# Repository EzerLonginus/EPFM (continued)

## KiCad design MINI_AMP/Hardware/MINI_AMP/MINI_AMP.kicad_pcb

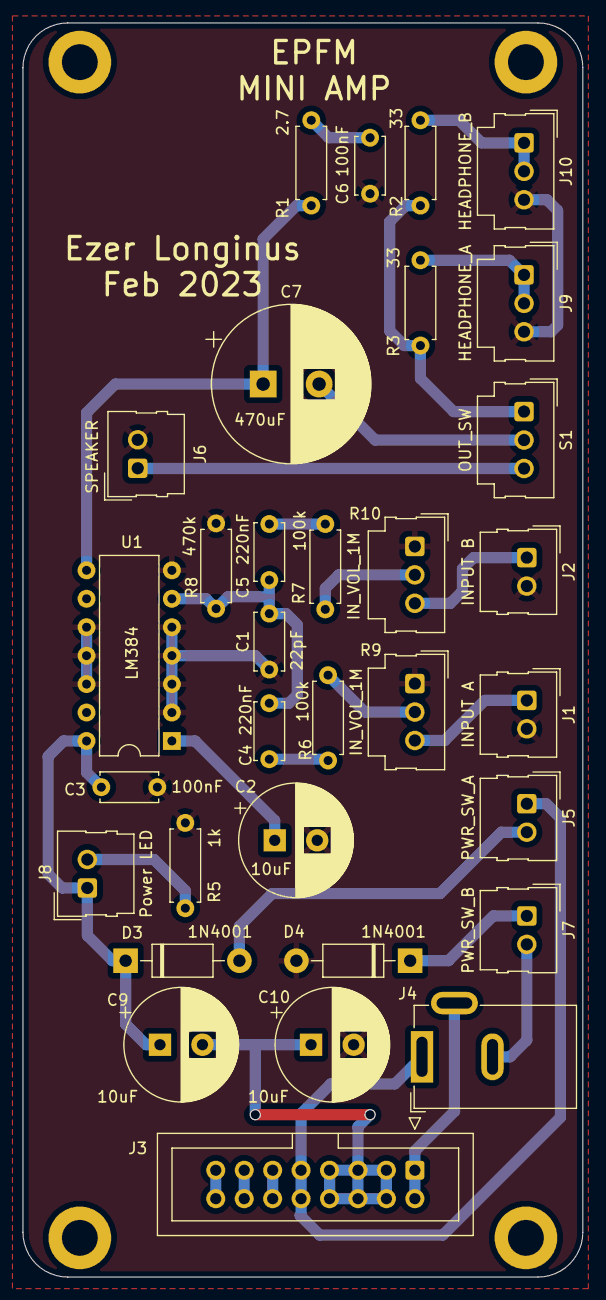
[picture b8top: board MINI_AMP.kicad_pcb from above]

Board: 2 copper layers, 50.0 x 112.0 mm, 36 parts (0 on the bottom side), 27 nets.

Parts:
C1: 22pF; C_Disc_D5.0mm_W2.5mm_P5.00mm
C2, C9, C10: 10uF; CP_Radial_D10.0mm_P3.80mm
C3, C6: 100nF; C_Disc_D5.0mm_W2.5mm_P5.00mm
C4, C5: 220nF; C_Disc_D5.0mm_W2.5mm_P5.00mm
C7: 470uF; CP_Radial_D14.0mm_P5.00mm
D3, D4: 1N4001; D_DO-41_SOD81_P10.16mm_Horizontal
H1, H2, H3, H4: MountingHole; MountingHole_3.2mm_M3_DIN965_Pad
J1: INPUT A; Molex_SL_171971-0002_1x02_P2.54mm_Vertical
J2: INPUT B; Molex_SL_171971-0002_1x02_P2.54mm_Vertical
J3: Conn_02x08_Odd_Even; IDC-Header_2x08_P2.54mm_Vertical
J4: Barrel_Jack_Switch; BarrelJack_GCT_DCJ200-10-A_Horizontal
J5: PWR_SW_A; Molex_SL_171971-0002_1x02_P2.54mm_Vertical
J6: SPEAKER; Molex_SL_171971-0002_1x02_P2.54mm_Vertical
J7: PWR_SW_B; Molex_SL_171971-0002_1x02_P2.54mm_Vertical
J8: Power LED; Molex_SL_171971-0002_1x02_P2.54mm_Vertical
J9: HEADPHONE_A; Molex_SL_171971-0003_1x03_P2.54mm_Vertical
J10: HEADPHONE_B; Molex_SL_171971-0003_1x03_P2.54mm_Vertical
R1: 2.7; R_Axial_DIN0207_L6.3mm_D2.5mm_P7.62mm_Horizontal
R2, R3: 33; R_Axial_DIN0207_L6.3mm_D2.5mm_P7.62mm_Horizontal
R5: 1k; R_Axial_DIN0207_L6.3mm_D2.5mm_P7.62mm_Horizontal
R6, R7: 100k; R_Axial_DIN0207_L6.3mm_D2.5mm_P7.62mm_Horizontal
R8: 470k; R_Axial_DIN0207_L6.3mm_D2.5mm_P7.62mm_Horizontal
R9, R10: IN_VOL_1M; Molex_SL_171971-0003_1x03_P2.54mm_Vertical
S1: OUT_SW; Molex_SL_171971-0003_1x03_P2.54mm_Vertical
U1: LM384; DIP-14_W7.62mm

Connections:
+5V: J3.11, J3.12
+12V: J3.9, J3.10, J4.1, J5.1
+24V: C3.2, C9.1, D3.1 (K), J8.1, U1.14 (VS)
-12V: J4.2, J7.2
CV: J3.13, J3.14
Earth: C1.1, C2.2, C3.1, C6.1, C10.2, D4.2 (A), J1.2, J2.2, J6.2, J9.3, J10.3, R5.1, R8.1, R9.1, R10.1, U1.2 (+), U1.3 (GND), U1.4 (GND), U1.5 (GND), U1.7 (GND), U1.10 (GND), U1.11 (GND), U1.12 (GND)
GATE: J3.15, J3.16
unnamed: C2.1, U1.1 (BYPASS)
unnamed: C1.2, C4.1, C5.1, R8.2, U1.6 (-)
unnamed: C6.2, R1.1
unnamed: C7.1, R1.2, U1.8
unnamed: C7.2, S1.2
unnamed: C9.2, C10.1, J3.3, J3.4, J3.5, J3.6, J3.7, J3.8
unnamed: D3.2 (A), J5.2
unnamed: D4.1 (K), J7.1
unnamed: J2.1, R10.3
unnamed: J3.1, J3.2, J4.3
unnamed: J6.1, S1.3
unnamed: J8.2, R5.2
unnamed: J9.1, J9.2, R3.1
unnamed: J10.1, J10.2, R2.1
unnamed: R2.2, R3.2, S1.1
unnamed: C4.2, R6.2
unnamed: C5.2, R7.2
unnamed: R6.1, R9.2
unnamed: J1.1, R9.3
unnamed: R7.1, R10.2

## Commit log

2023-01-26 Panel and Initial EE commit
2023-01-26 Schematic V01
2023-01-26 File Name Corrections
2023-01-26 Initial Board Layout
2023-01-26 Production Files for V01
2023-01-30 Metronome Initial Commit
2023-01-30 Initial Metronome Layout Commit
2023-01-31 Initial Passive Tone Control Schematic
2023-02-03 Initial Headphone Amp Commit
2023-02-16 PREAMP V02 and HEADPHONE AMP
2023-02-16 PREAMP Production Files
2023-02-16 PREAMP 3D Prints
2023-02-16 Production Files Fixed
2023-02-18 Preamp Panel New VU Meter
2023-02-21 Metronome CAD files
2023-02-27 Ultra Fuzz and PTC files
2023-02-27 Updated main README.md
2023-02-27 reformatted README
2023-02-27 Ultra Fuzz Gerber Files
2023-02-27 fixed Ultra Fuzz folder convention
2023-03-07 Added Ultra Fuzz and Bass Fuzz
